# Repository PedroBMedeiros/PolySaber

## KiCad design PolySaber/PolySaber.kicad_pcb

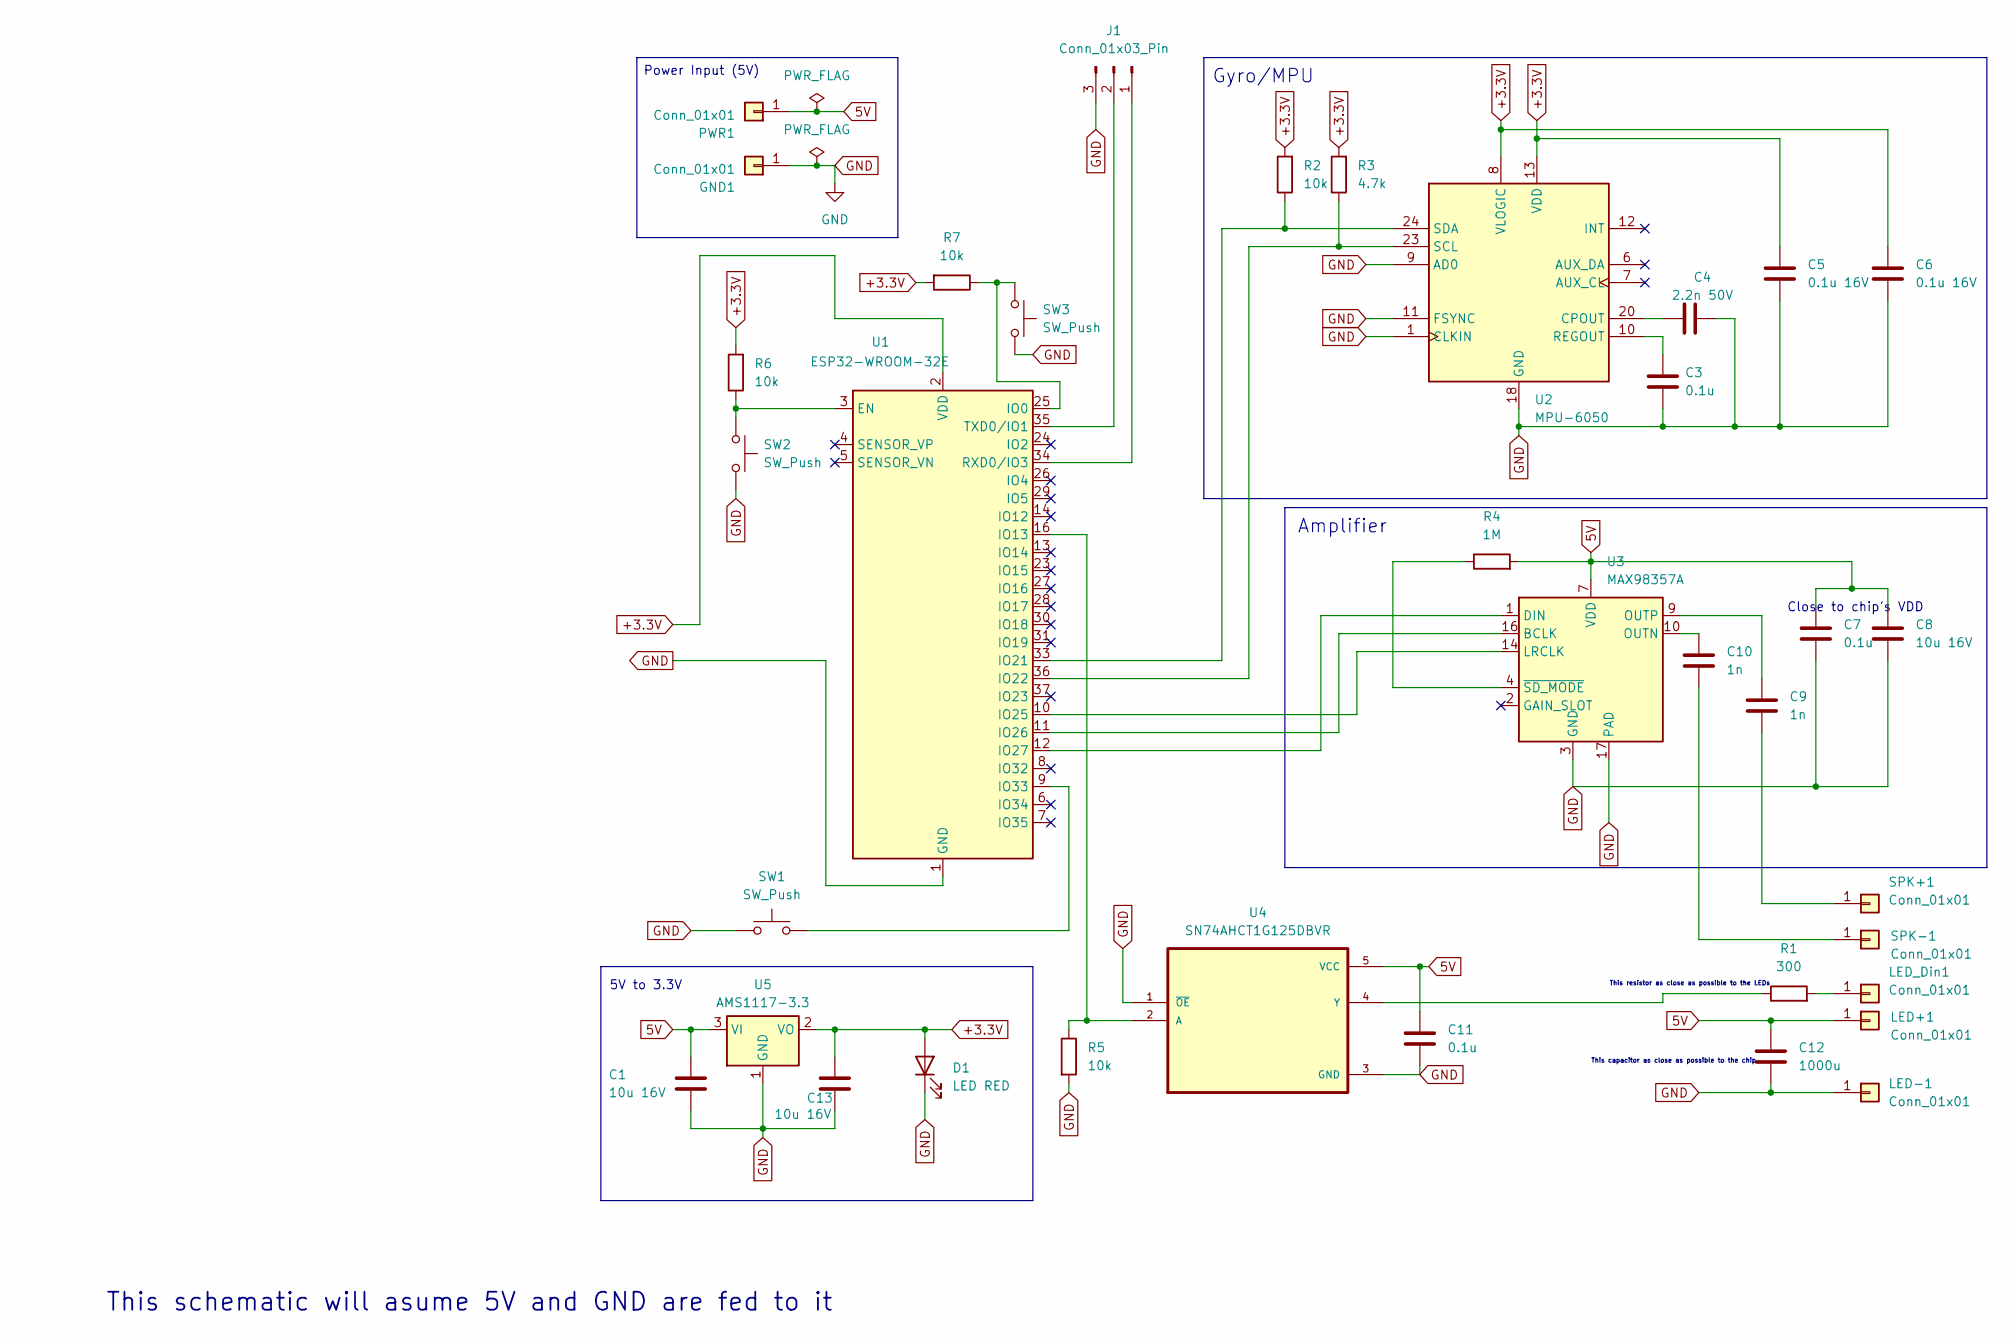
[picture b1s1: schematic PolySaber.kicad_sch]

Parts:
C1, C8, C13: 10u 16V; C_0603_1608Metric_Pad1.08x0.95mm_HandSolder; LCSC C19702
C3: 0.1u; C_0201_0603Metric_Pad0.64x0.40mm_HandSolder; LCSC C14663
C4: 2.2n 50V; C_0603_1608Metric_Pad1.08x0.95mm_HandSolder; LCSC C1604
C5, C6: 0.1u 16V; C_0603_1608Metric_Pad1.08x0.95mm_HandSolder; LCSC C14663
C7, C11: 0.1u; C_0603_1608Metric_Pad1.08x0.95mm_HandSolder; LCSC C14663
C9, C10: 1n; C_0201_0603Metric_Pad0.64x0.40mm_HandSolder; LCSC C1588
C12: 1000u; CP_Radial_D10.0mm_P5.00mm; LCSC C439782
D1: LED RED; LED_0603_1608Metric_Pad1.05x0.95mm_HandSolder; LCSC C2286
GND1: Conn_01x01; TestPoint_Pad_4.0x4.0mm
J1: Conn_01x03_Pin; PinHeader_1x03_P2.54mm_Vertical; LCSC C49257
LED+1: Conn_01x01; TestPoint_Pad_4.0x4.0mm
LED-1: Conn_01x01; TestPoint_Pad_4.0x4.0mm
LED_Din1: Conn_01x01; TestPoint_Pad_4.0x4.0mm
PWR1: Conn_01x01; TestPoint_Pad_4.0x4.0mm
R1: 300; R_0603_1608Metric_Pad0.98x0.95mm_HandSolder; LCSC C23025
R2, R5, R6, R7: 10k; R_0603_1608Metric_Pad0.98x0.95mm_HandSolder; LCSC C25804
R3: 4.7k; R_0603_1608Metric_Pad0.98x0.95mm_HandSolder; LCSC C23162
R4: 1M; R_0603_1608Metric_Pad0.98x0.95mm_HandSolder; LCSC C22935
SPK+1: Conn_01x01; TestPoint_Pad_4.0x4.0mm
SPK-1: Conn_01x01; TestPoint_Pad_4.0x4.0mm
SW1, SW2, SW3: SW_Push; SW_Tactile_SPST_NO_Straight_CK_PTS636Sx25SMTRLFS; LCSC C2689642
U1: ESP32-WROOM-32E; LCSC C701343
U2: MPU-6050; InvenSense_QFN-24_4x4mm_P0.5mm; LCSC C24112
U3: MAX98357A; TQFN-16-1EP_3x3mm_P0.5mm_EP1.23x1.23mm; LCSC C910544
U4: SN74AHCT1G125DBVR; SOT95P280X145-5N; LCSC C7484
U5: AMS1117-3.3; SOT-223-3_TabPin2; LCSC C6186

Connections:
5V: C1.1, C7.1, C8.1, C11.1, C12.1, LED+1.1, PWR1.1, R4.2, U3.7 (VDD), U3.8 (VDD), U4.5 (VCC), U5.3 (VI)
+3.3V: C5.1, C6.1, C13.1, D1.2 (A), R2.2, R3.2, R6.2, R7.2, U1.2 (VDD), U2.8 (VLOGIC), U2.13 (VDD), U5.2 (VO)
GND: C1.2, C3.2, C4.2, C5.2, C6.2, C7.2, C8.2, C11.2, C12.2, C13.2, D1.1 (K), GND1.1, J1.3, LED-1.1, R5.2, SW1.1, SW2.2, SW3.2, U1.1 (GND), U1.15 (GND), U1.38 (GND), U1.39 (GND), U2.1 (CLKIN), U2.9 (AD0), U2.11 (FSYNC), U2.18 (GND), U3.3 (GND), U3.11 (GND), U3.15 (GND), U3.17 (PAD), U4.1 (~OE), U4.3 (GND), U5.1 (GND)
unnamed: J1.1, U1.34 (RXD0/IO3)
unnamed: J1.2, U1.35 (TXD0/IO1)
unnamed: LED_Din1.1, R1.2
unnamed: C9.2, SPK+1.1
unnamed: C10.2, SPK-1.1
unnamed: R6.1, SW2.1, U1.3 (EN)
unnamed: R7.1, SW3.1, U1.25 (IO0)
unnamed: R5.1, U1.16 (IO13), U4.2 (A)
unnamed: R2.1, U1.33 (IO21), U2.24 (SDA)
unnamed: R3.1, U1.36 (IO22), U2.23 (SCL)
unnamed: U1.10 (IO25), U3.14 (LRCLK)
unnamed: U1.11 (IO26), U3.16 (BCLK)
unnamed: U1.12 (IO27), U3.1 (DIN)
unnamed: SW1.2, U1.9 (IO33)
unnamed: C4.1, U2.20 (CPOUT)
unnamed: C3.1, U2.10 (REGOUT)
unnamed: C10.1, U3.10 (OUTN)
unnamed: C9.1, U3.9 (OUTP)
unnamed: R4.1, U3.4 (~SD_MODE)
unnamed: R1.1, U4.4 (Y)

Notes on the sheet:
This schematic will asume 5V and GND are fed to it
Close to chip's VDD
This capacitor as close as possible to the chip
5V to 3.3V
This resistor as close as possible to the LEDs
Gyro/MPU
Amplifier
Power Input (5V)

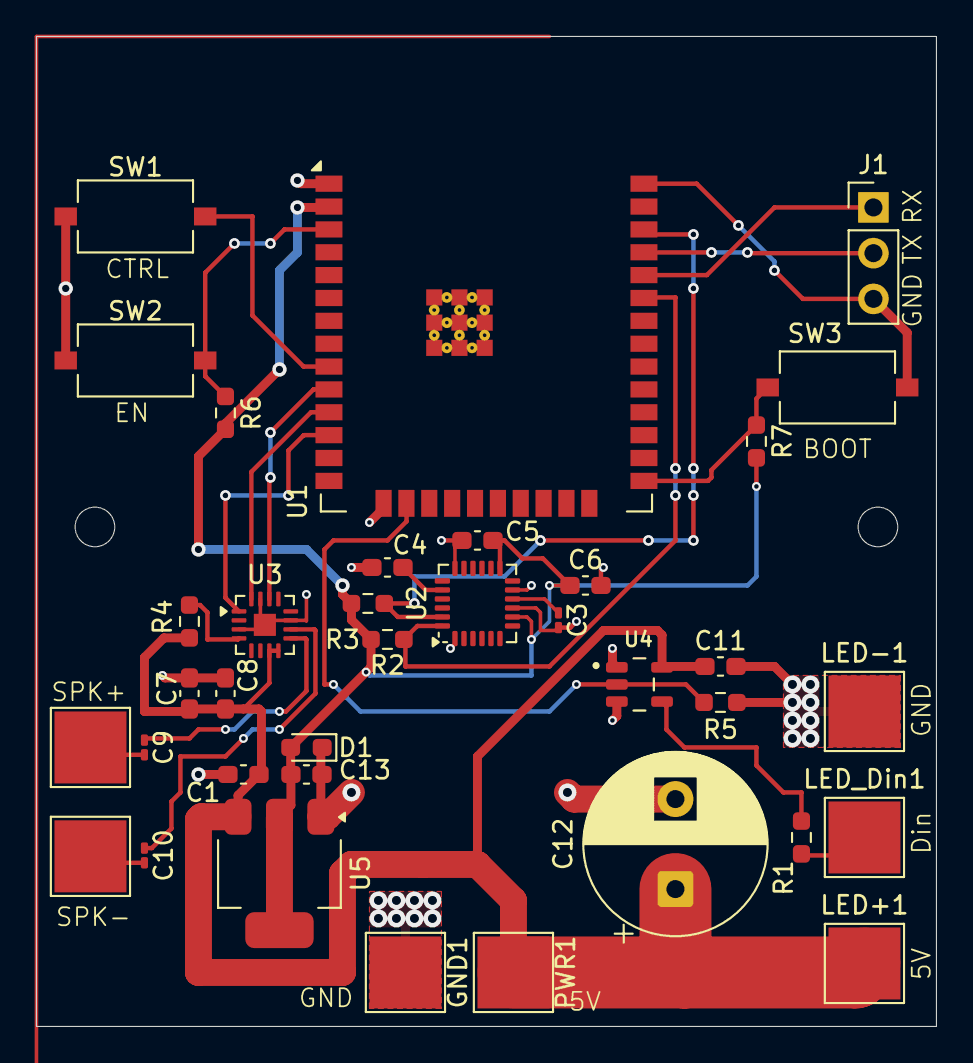
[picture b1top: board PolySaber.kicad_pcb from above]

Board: 2 copper layers, 50.0 x 55.0 mm, 36 parts (0 on the bottom side), 23 nets.

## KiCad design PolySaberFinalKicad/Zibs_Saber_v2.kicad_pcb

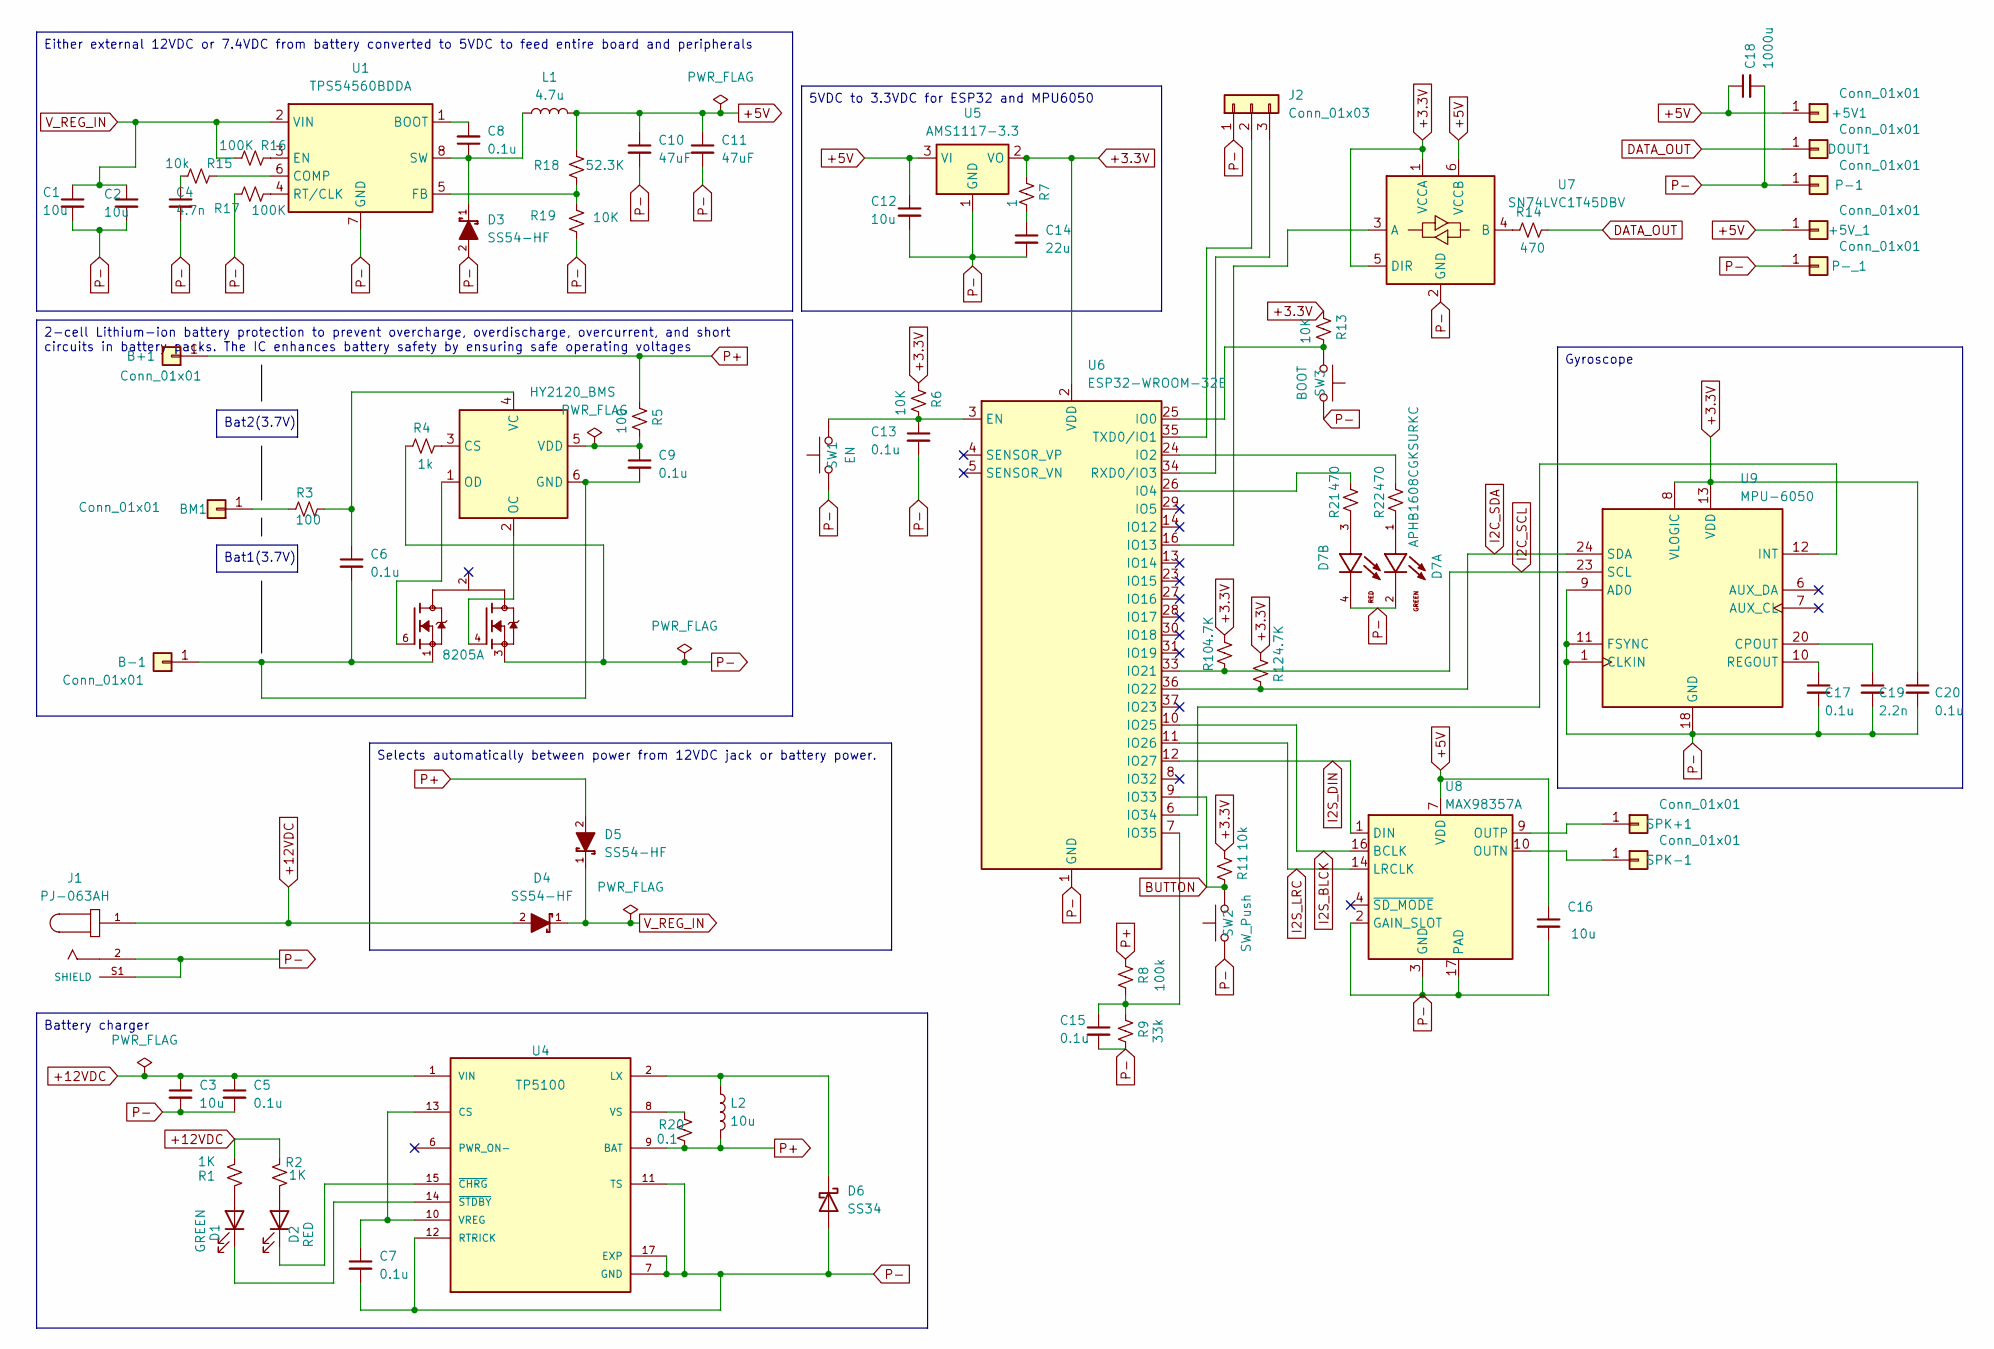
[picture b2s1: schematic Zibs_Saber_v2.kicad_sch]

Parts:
+5V1, +5V_1: Conn_01x01; TestPoint_Pad_4.0x4.0mm
B+1: Conn_01x01; TestPoint_Pad_4.0x4.0mm
B-1: Conn_01x01; TestPoint_Pad_4.0x4.0mm
BM1: Conn_01x01; TestPoint_Pad_4.0x4.0mm
C1, C2: 10u; C_1210_3225Metric; MANUFACTURER_PART_NUMBER CL32B106KBJNNNE; LCSC C18739
C3: 10u; C_1206_3216Metric; MANUFACTURER_PART_NUMBER CL31A106KAHNNNE; LCSC C9807
C4: 4.7n; C_0805_2012Metric_Pad1.18x1.45mm_HandSolder; MPN C50131; LCSC C50131
C5, C6, C7, C8, C9, C13, C15, C17, C20: 0.1u; C_0805_2012Metric_Pad1.18x1.45mm_HandSolder; MPN C126469; LCSC C126469
C10, C11: 47uF; C_1210_3225Metric; MPN C77101; LCSC C77101
C12, C16: 10u; C_0805_2012Metric_Pad1.18x1.45mm_HandSolder; MPN C15850; LCSC C15850
C14: 22u; C_0805_2012Metric_Pad1.18x1.45mm_HandSolder; MPN C45783; LCSC C45783
C18: 1000u; CP_Radial_D8.0mm_P3.50mm; MANUFACTURER_PART_NUMBER EEU-FR1J101B; LCSC C439782
C19: 2.2n; C_0805_2012Metric_Pad1.18x1.45mm_HandSolder; MPN C28260; LCSC C28260
D1: GREEN; LED_0805_2012Metric; MPN C2297; LCSC C2297
D2: RED; LED_0805_2012Metric; MPN C2295; LCSC C2295
D3, D4, D5: SS54-HF; SMCDO-214AB_CIP-M; MOUSER_PART_NUMBER 750-SS54-HF
D6: SS34; D_SMA; MPN C8678; LCSC C8678
D7: APHB1608CGKSURKC; LED_APHB1608CGKSURKC; PARTREV V.5A; LCSC C6506245
DOUT1: Conn_01x01; TestPoint_Pad_4.0x4.0mm
J1: PJ-063AH; CUI_PJ-063AH; PARTREV 1.02; LCSC C2928097
J2: Conn_01x03; PinHeader_1x03_P2.54mm_Horizontal; MPN C92159; LCSC C92159
L1: 4.7u; L_7.3x7.3_H4.5; MPN C136201; LCSC C136201
L2: 10u; L_7.3x7.3_H4.5; MPN C879412; LCSC C879412
P-1: Conn_01x01; TestPoint_Pad_4.0x4.0mm
P-_1: Conn_01x01; TestPoint_Pad_4.0x4.0mm
R1, R2: 1K; R_0805_2012Metric_Pad1.20x1.40mm_HandSolder; MPN C17513; LCSC C17513
R3, R5: 100; R_0805_2012Metric_Pad1.20x1.40mm_HandSolder; MPN C17408; LCSC C17408
R4: 1k; R_0805_2012Metric_Pad1.20x1.40mm_HandSolder; MPN C17513; LCSC C17513
R6, R13: 10K; R_0805_2012Metric_Pad1.20x1.40mm_HandSolder; MPN C17414; LCSC C17414
R7: 1; R_0805_2012Metric_Pad1.20x1.40mm_HandSolder; MPN C17376; LCSC C17376
R8: 100k; R_0805_2012Metric_Pad1.20x1.40mm_HandSolder; MPN C96346; LCSC C96346
R9: 33k; R_0805_2012Metric_Pad1.20x1.40mm_HandSolder; MPN C17633; LCSC C17633
R10, R12: 4.7K; R_0805_2012Metric_Pad1.20x1.40mm_HandSolder; MPN C17673; LCSC C17673
R11: 10k; R_0805_2012Metric_Pad1.20x1.40mm_HandSolder; MPN C17414; LCSC C17414
R14: 470; R_0805_2012Metric_Pad1.20x1.40mm_HandSolder; MPN C17710; LCSC C17710
R15: 10k; R_1206_3216Metric; MPN C17902; LCSC C17902
R16, R17: 100K; R_1206_3216Metric; MPN C17900; LCSC C17900
R18: 52.3K; R_1206_3216Metric; MPN C245568; LCSC C245568
R19: 10K; R_1206_3216Metric; MPN C17902; LCSC C17902
R20: 0.1; R_1206_3216Metric; MPN C346768; LCSC C346768
R21, R22: 470; R_0805_2012Metric_Pad1.20x1.40mm_HandSolder; MPN C206545; LCSC C206545
SPK+1: Conn_01x01; TestPoint_Pad_4.0x4.0mm
SPK-1: Conn_01x01; TestPoint_Pad_4.0x4.0mm
SW1: EN; SW_Tactile_SPST_NO_Straight_CK_PTS636Sx25SMTRLFS; MPN C2800443; LCSC C2800443
SW2: SW_Push; SW_PUSH_6mm; MPN C93157; LCSC C93157
SW3: BOOT; SW_Tactile_SPST_NO_Straight_CK_PTS636Sx25SMTRLFS; MPN C2800443; LCSC C2800443
U1: TPS54560BDDA; Texas_R-PDSO-G8_EP2.95x4.9mm_Mask2.4x3.1mm_ThermalVias; MPN C1850354; LCSC C1850354
U2: 8205A; SOT-23-6_Handsoldering; PARTREV NA; LCSC C181097
U3: HY2120_BMS; SOT-23-6; MPN C116509; LCSC C116509
U4: TP5100; QFN-16-1EP_4x4mm_P0.65mm_EP2.7x2.7mm; PARTREV 2.3; LCSC C379389
U5: AMS1117-3.3; SOT-223-3_TabPin2; MPN C347222; LCSC C347222
U6: ESP32-WROOM-32E; MPN C701342; LCSC C701342
U7: SN74LVC1T45DBV; SOT-23-6; MPN C7843; LCSC C7843
U8: MAX98357A; TQFN-16-1EP_3x3mm_P0.5mm_EP1.23x1.23mm; MPN C910544; LCSC C910544
U9: MPU-6050; InvenSense_QFN-24_4x4mm_P0.5mm; MPN C24112; LCSC C24112

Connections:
+3.3V: C20.1, R6.1, R7.1, R10.1, R11.1, R12.1, R13.1, U5.2 (VO), U6.2 (VDD), U7.1 (VCCA), U7.5 (DIR), U9.8 (VLOGIC), U9.13 (VDD)
+5V: +5V1.1, +5V_1.1, C10.1, C11.1, C12.1, C16.1, C18.1, L1.2, R18.1, U5.3 (VI), U7.6 (VCCB), U8.7 (VDD), U8.8 (VDD)
+12VDC: C3.1, C5.1, D4.2, J1.1, R1.1, R2.1, U4.1 (VIN), U4.4 (VIN), U4.5 (VIN), U4.16 (VIN)
BUTTON: R11.2, SW2.2, U6.9 (IO33)
DATA_OUT: DOUT1.1, R14.2
I2C_SCL: R10.2, U6.33 (IO21), U9.23 (SCL)
I2C_SDA: R12.2, U6.36 (IO22), U9.24 (SDA)
I2S_BLCK: U6.10 (IO25), U8.16 (BCLK)
I2S_DIN: U6.12 (IO27), U8.1 (DIN)
I2S_LRC: U6.11 (IO26), U8.14 (LRCLK)
unnamed: B-1.1, C6.2, C9.2, U2.1, U3.6 (GND)
unnamed: BM1.1, R3.1
unnamed: C4.1, R15.2
unnamed: C14.1, R7.2
unnamed: D1.2 (A), R1.2
unnamed: D1.1 (K), U4.14 (~STDBY)
unnamed: D2.2 (A), R2.2
unnamed: D2.1 (K), U4.15 (~CHRG)
unnamed: D6.1 (K), L2.1, U4.2 (LX), U4.3 (LX)
unnamed: D7.1, R22.2
unnamed: D7.3, R21.2
unnamed: J2.2, U6.35 (TXD0/IO1)
unnamed: J2.3, U6.34 (RXD0/IO3)
unnamed: SPK+1.1, U8.9 (OUTP)
unnamed: SPK-1.1, U8.10 (OUTN)
unnamed: C8.2, U1.1 (BOOT)
unnamed: R15.1, U1.6 (COMP)
unnamed: R16.1, U1.3 (EN)
unnamed: R18.2, R19.1, U1.5 (FB)
unnamed: R17.1, U1.4 (RT/CLK)
unnamed: C8.1, D3.1, L1.1, U1.8 (SW)
unnamed: R4.2, U3.3 (CS)
unnamed: U2.4, U3.2 (OC)
unnamed: U2.6, U3.1 (OD)
unnamed: C6.1, R3.2, U3.4 (VC)
unnamed: C9.1, R5.2, U3.5 (VDD)
unnamed: C7.1, U4.10 (VREG), U4.13 (CS)
unnamed: R20.1, U4.8 (VS)
unnamed: C13.1, R6.2, SW1.2, U6.3 (EN)
unnamed: R13.2, SW3.1, U6.25 (IO0)
unnamed: R22.1, U6.24 (IO2)
unnamed: R21.1, U6.26 (IO4)
unnamed: U6.16 (IO13), U7.3 (A)
unnamed: U6.6 (IO34), U9.12 (INT)
unnamed: C15.1, R8.2, R9.1, U6.7 (IO35)
unnamed: R14.1, U7.4 (B)
unnamed: C19.1, U9.20 (CPOUT)
unnamed: C17.1, U9.10 (REGOUT)
P+: B+1.1, D5.2, L2.2, R5.1, R8.1, R20.2, U4.9 (BAT)
P-: C1.2, C2.2, C3.2, C4.2, C5.2, C7.2, C10.2, C11.2, C12.2, C13.2, C14.2, C15.2, C16.2, C17.2, C18.2, C19.2, C20.2, D3.2, D6.2 (A), D7.2, D7.4, J1.2, J1.S1 (SHIELD), J1.S2 (SHIELD), J2.1, P-1.1, P-_1.1, R4.1, R9.2, R17.2, R19.2, SW1.1, SW2.1, SW3.2, U1.7 (GND), U1.9 (GND), U2.3, U4.7 (GND), U4.11 (TS), U4.12 (RTRICK), U4.17 (EXP), U5.1 (GND), U6.1 (GND), U6.15 (GND), U6.38 (GND), U6.39 (GND), U7.2 (GND), U8.2 (GAIN_SLOT), U8.3 (GND), U8.11 (GND), U8.15 (GND), U8.17 (PAD), U9.1 (CLKIN), U9.9 (AD0), U9.11 (FSYNC), U9.18 (GND)
V_REG_IN: C1.1, C2.1, D4.1, D5.1, R16.2, U1.2 (VIN)

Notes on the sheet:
2-cell Lithium-ion battery protection to prevent overcharge, overdischarge, overcurrent, and short circuits in battery packs. The IC enhances battery safety by ensuring safe operating voltages
Either external 12VDC or 7.4VDC from battery converted to 5VDC to feed entire board and peripherals
Bat1(3.7V)
Selects automatically between power from 12VDC jack or battery power.
Battery charger
Bat2(3.7V)
Gyroscope
5VDC to 3.3VDC for ESP32 and MPU6050

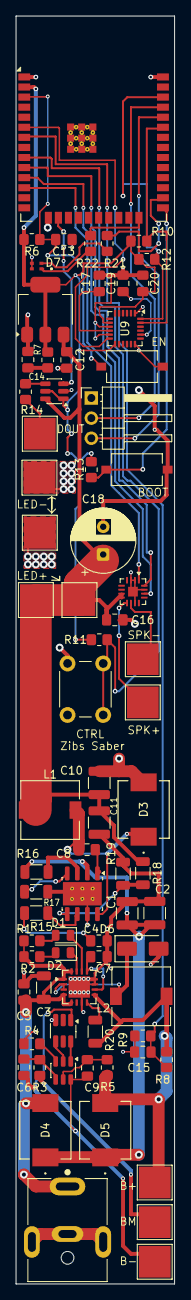
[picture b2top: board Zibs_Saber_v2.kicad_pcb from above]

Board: 2 copper layers, 20.0 x 160.0 mm, 75 parts (0 on the bottom side), 51 nets.

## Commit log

2026-06-04 Added Firmware Files
2026-06-04 Kicad file Upload
2026-06-04 Final Revision Kicad Upload
2026-06-04 First PCB Revision
2026-06-04 First Revision of PCB
2026-06-04 PolySaber Firmware
